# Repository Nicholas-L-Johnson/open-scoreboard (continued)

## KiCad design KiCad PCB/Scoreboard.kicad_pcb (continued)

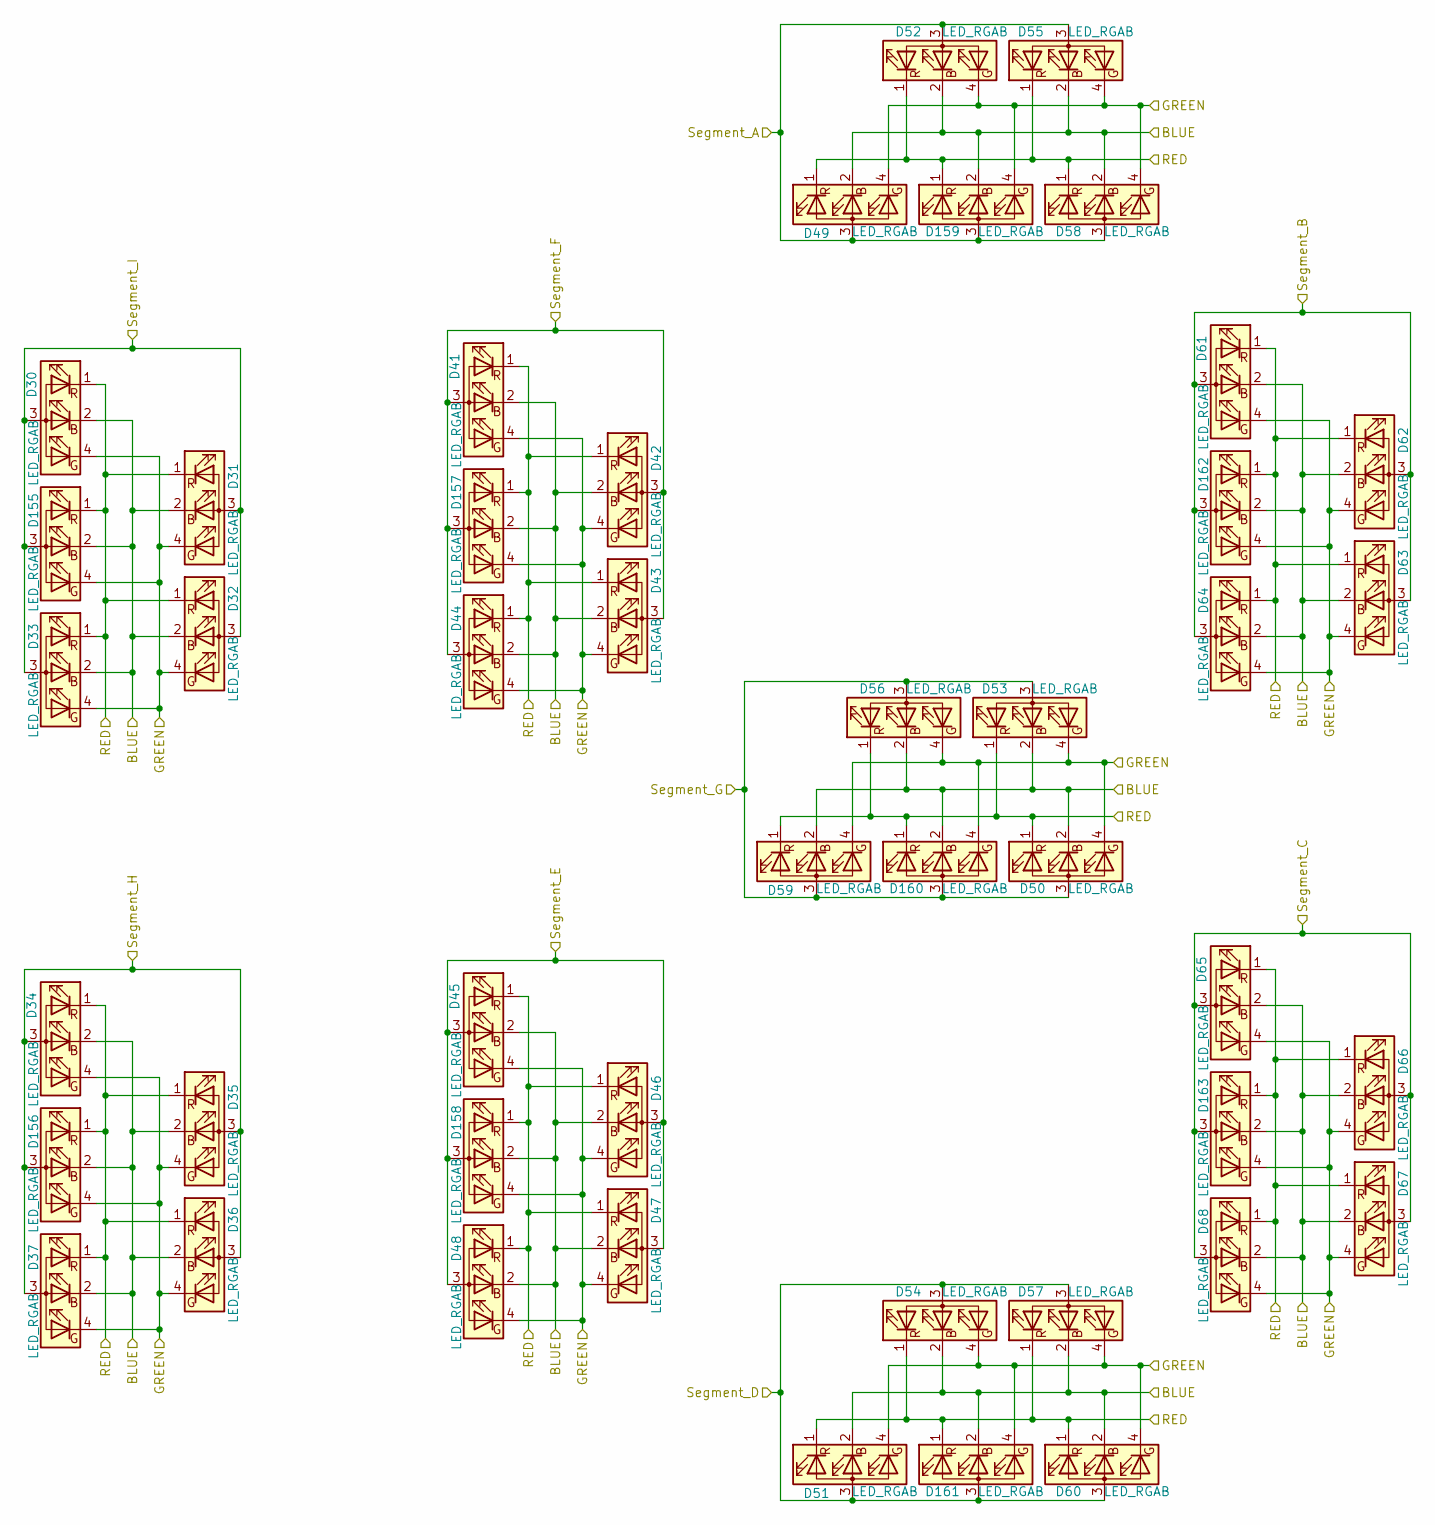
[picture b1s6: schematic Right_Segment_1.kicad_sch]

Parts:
D30, D31, D32, D33, D34, D35, D36, D37, D41, D42, D43, D44, D45, D46, D47, D48, D49, D50, D51, D52, D53, D54, D55, D56, D57, D58, D59, D60, D61, D62, D63, D64, D65, D66, D67, D68, D155, D156, D157, D158, D159, D160, D161, D162, D163: LED_RGAB; RGB_LED_NH-B2020RGBA-HF; Part Number NH-B2020RGBA-HF; LCSC Part Number C2874116

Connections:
BLUE_RIGHT_1: D30.2 (GK), D31.2 (GK), D32.2 (GK), D33.2 (GK), D34.2 (GK), D35.2 (GK), D36.2 (GK), D37.2 (GK), D41.2 (GK), D42.2 (GK), D43.2 (GK), D44.2 (GK), D45.2 (GK), D46.2 (GK), D47.2 (GK), D48.2 (GK), D49.2 (GK), D50.2 (GK), D51.2 (GK), D52.2 (GK), D53.2 (GK), D54.2 (GK), D55.2 (GK), D56.2 (GK), D57.2 (GK), D58.2 (GK), D59.2 (GK), D60.2 (GK), D61.2 (GK), D62.2 (GK), D63.2 (GK), D64.2 (GK), D65.2 (GK), D66.2 (GK), D67.2 (GK), D68.2 (GK), D155.2 (GK), D156.2 (GK), D157.2 (GK), D158.2 (GK), D159.2 (GK), D160.2 (GK), D161.2 (GK), D162.2 (GK), D163.2 (GK); also elsewhere on the board
GREEN_RIGHT_1: D30.4 (BK), D31.4 (BK), D32.4 (BK), D33.4 (BK), D34.4 (BK), D35.4 (BK), D36.4 (BK), D37.4 (BK), D41.4 (BK), D42.4 (BK), D43.4 (BK), D44.4 (BK), D45.4 (BK), D46.4 (BK), D47.4 (BK), D48.4 (BK), D49.4 (BK), D50.4 (BK), D51.4 (BK), D52.4 (BK), D53.4 (BK), D54.4 (BK), D55.4 (BK), D56.4 (BK), D57.4 (BK), D58.4 (BK), D59.4 (BK), D60.4 (BK), D61.4 (BK), D62.4 (BK), D63.4 (BK), D64.4 (BK), D65.4 (BK), D66.4 (BK), D67.4 (BK), D68.4 (BK), D155.4 (BK), D156.4 (BK), D157.4 (BK), D158.4 (BK), D159.4 (BK), D160.4 (BK), D161.4 (BK), D162.4 (BK), D163.4 (BK); also elsewhere on the board
RED_RIGHT_1: D30.1 (RK), D31.1 (RK), D32.1 (RK), D33.1 (RK), D34.1 (RK), D35.1 (RK), D36.1 (RK), D37.1 (RK), D41.1 (RK), D42.1 (RK), D43.1 (RK), D44.1 (RK), D45.1 (RK), D46.1 (RK), D47.1 (RK), D48.1 (RK), D49.1 (RK), D50.1 (RK), D51.1 (RK), D52.1 (RK), D53.1 (RK), D54.1 (RK), D55.1 (RK), D56.1 (RK), D57.1 (RK), D58.1 (RK), D59.1 (RK), D60.1 (RK), D61.1 (RK), D62.1 (RK), D63.1 (RK), D64.1 (RK), D65.1 (RK), D66.1 (RK), D67.1 (RK), D68.1 (RK), D155.1 (RK), D156.1 (RK), D157.1 (RK), D158.1 (RK), D159.1 (RK), D160.1 (RK), D161.1 (RK), D162.1 (RK), D163.1 (RK); also elsewhere on the board
Segment_A: D49.3 (A), D52.3 (A), D55.3 (A), D58.3 (A), D159.3 (A); also elsewhere on the board
Segment_B: D61.3 (A), D62.3 (A), D63.3 (A), D64.3 (A), D162.3 (A); also elsewhere on the board
Segment_C: D65.3 (A), D66.3 (A), D67.3 (A), D68.3 (A), D163.3 (A); also elsewhere on the board
Segment_D: D51.3 (A), D54.3 (A), D57.3 (A), D60.3 (A), D161.3 (A); also elsewhere on the board
Segment_E: D45.3 (A), D46.3 (A), D47.3 (A), D48.3 (A), D158.3 (A); also elsewhere on the board
Segment_F: D41.3 (A), D42.3 (A), D43.3 (A), D44.3 (A), D157.3 (A); also elsewhere on the board
Segment_G: D50.3 (A), D53.3 (A), D56.3 (A), D59.3 (A), D160.3 (A); also elsewhere on the board
Segment_H: D34.3 (A), D35.3 (A), D36.3 (A), D37.3 (A), D156.3 (A); also elsewhere on the board
Segment_I: D30.3 (A), D31.3 (A), D32.3 (A), D33.3 (A), D155.3 (A); also elsewhere on the board

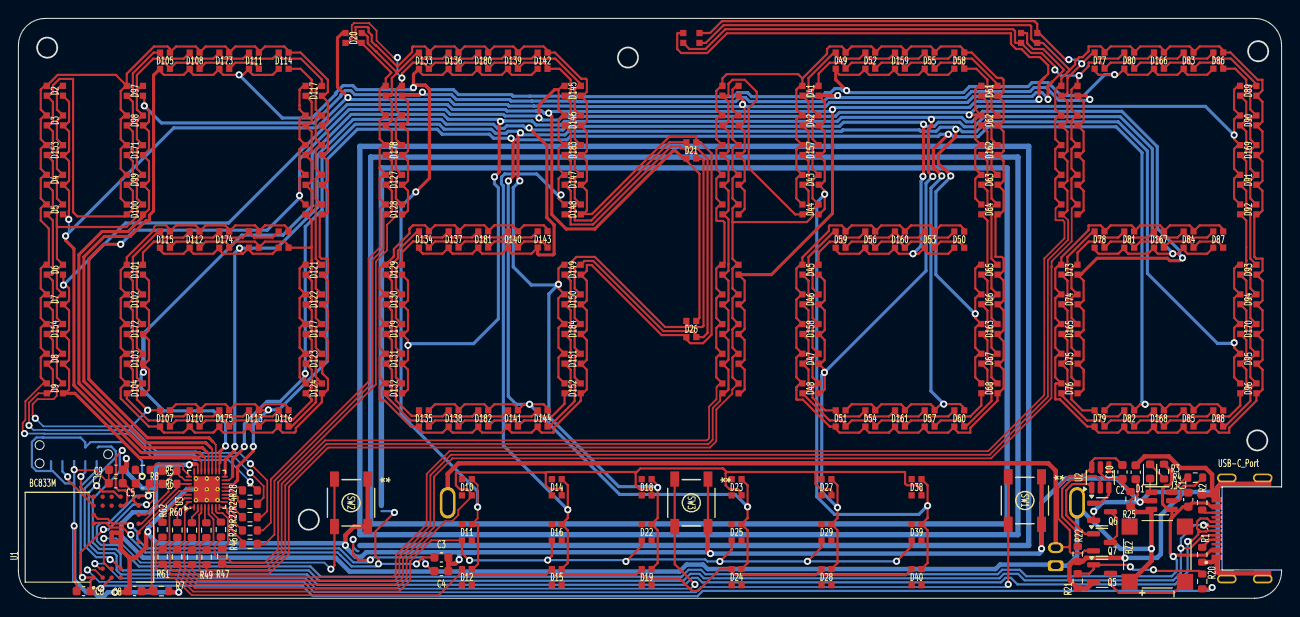
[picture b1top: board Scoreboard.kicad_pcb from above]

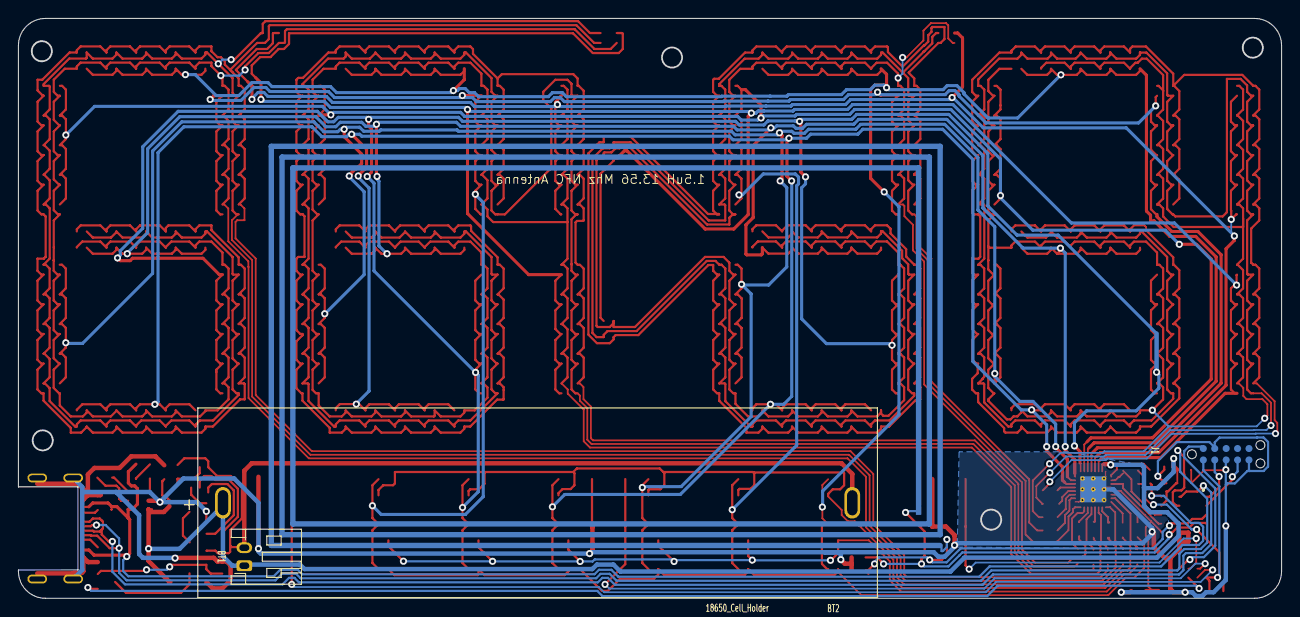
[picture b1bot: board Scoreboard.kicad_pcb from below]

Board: 2 copper layers, 140.5 x 64.5 mm, 237 parts (4 on the bottom side), 72 nets.

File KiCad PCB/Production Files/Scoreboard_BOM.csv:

"#","Reference","Value","Datasheet","Footprint","Qty","Manufacturer","Package","Price","Vendor","DNP","Notes","Part Number","LCSC Part Number","Website"
"1","BT2","18650_Cell_Holder","https://www.lcsc.com/datasheet/lcsc_datasheet_2211291730_MYO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","User_Footprints:18650_Cell_Holder","1","MYOUNG","THT",".42","LCSC","DNP","","BH-18650-A1AJ005","C5290176","https://www.lcsc.com/product-detail/Button-And-Strip-Battery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"
"2","BZ2","Buzzer","https://www.lcsc.com/datasheet/lcsc_datasheet_2410010301_KEL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","User_Footprints:XDCR_CMT-7525-80-SMT-TR","1","KELIKING","SMD",".4741","LCSC","","2-4.5V 85dB 2.731kHz","KLJ-7525-3627","C189208","https://www.lcsc.com/product-detail/Buzzers_KELIKING-KLJ-752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"
"3","C1,C2,C9","1u","https://datasheet.lcsc.com/lcsc/2209191700_Samsung-Electro-M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","User_Footprints:C_0603_1608Metric","3","Samsung Electro-Mechanics","0603",".0032","LCSC","","16V 10%","CL10A105KO8NNNC","C1592","https://www.lcsc.com/product-detail/Multilayer-Ceramic-Capac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"
"4","C3,C4","18p","https://datasheet.lcsc.com/lcsc/2208181800_FOJAN-FCC0603N180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","User_Footprints:C_0603_1608Metric","2","FOJAN","0603",".0027","LCSC","","50V 5%","FCC0603N180J500CT","C5137620","https://www.lcsc.com/product-detail/Multilayer-Ceramic-Capac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"
"5","C5,C6","4u7","https://datasheet.lcsc.com/lcsc/2208051100_HRE-CSA0603X5R475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","User_Footprints:C_0603_1608Metric","2","HRE","0603",".0050","LCSC","","6.3V 10%","CGA0603X5R475K6R3JT","C7503506","https://www.lcsc.com/product-detail/Multilayer-Ceramic-Capac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"
"6","C7,C8,C10","100n","https://datasheet.lcsc.com/lcsc/2304140030_Samsung-Electro-M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","Capacitor_SMD:C_0603_1608Metric","3","Samsung Electro-Mechanics","0603",".0028","LCSC","","25V 10%","CL10B104KA8NNNC","C1590","https://www.lcsc.com/product-detail/Multilayer-Ceramic-Capac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"
"7","D1","LED","https://www.lcsc.com/datasheet/lcsc_datasheet_2402181505_XIN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","LED_SMD:LED_0603_1608Metric","1","XINGLIGHT","0603",".003","LCSC","","20mA","XL-1608SURC-06","C965799","https://www.lcsc.com/product-detail/span-style-background-co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"
"8","D2,D3,D4,D5,D6,D7,D8,D9,D10,D11,D12,D13,D14,D15,D16,D17,D18,D19,D20,D21,D22,D23,D24,D25,D26,D27,D28,D29,D30,D31,D32,D33,D34,D35,D36,D37,D38,D39,D40,D41,D42,D43,D44,D45,D46,D47,D48,D49,D50,D51,D52,D53,D54,D55,D56,D57,D58,D59,D60,D61,D62,D63,D64,D65,D66,D67,D68,D69,D70,D71,D72,D73,D74,D75,D76,D77,D78,D79,D80,D81,D82,D83,D84,D85,D86,D87,D88,D89,D90,D91,D92,D93,D94,D95,D96,D97,D98,D99,D100,D101,D102,D103,D104,D105,D106,D107,D108,D109,D110,D111,D112,D113,D114,D115,D116,D117,D118,D119,D120,D121,D122,D123,D124,D125,D126,D127,D128,D129,D130,D131,D132,D133,D134,D135,D136,D137,D138,D139,D140,D141,D142,D143,D144,D145,D146,D147,D148,D149,D150,D151,D152,D153,D154,D155,D156,D157,D158,D159,D160,D161,D162,D163,D164,D165,D166,D167,D168,D169,D170,D171,D172,D173,D174,D175,D176,D177,D178,D179,D180,D181,D182,D183,D184","LED_RGAB","https://datasheet.lcsc.com/lcsc/2108150330_Foshan-NationStar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","User_Footprints:RGB_LED_NH-B2020RGBA-HF","183","Foshan NationStar Optoelectronics","LED RGAB 2020",".0081","LCSC","","SMD","NH-B2020RGBA-HF","C2874116","https://www.lcsc.com/product-detail/Light-Emitting-Diodes-LE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"
"9","J2","USB-C_Port","https://www.lcsc.com/datasheet/lcsc_datasheet_2312191005_G-S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","User_Footprints:GCT_USB4110GFA","1","G-Switch","SMD",".0952","LCSC","","5A","GT-USB-7014A","C963371","https://www.lcsc.com/product-detail/USB-Connectors_G-Switch-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"
"10","J3","TP4057","https://www.vishay.com/docs/83316/sot236l.pdf","User_Footprints:SOT-23-6","1","YONGYUTAI","SOT-23-6L",".0265","LCSC","","0.3V-6.5V 600mA","TP4057","C20199358","https://www.lcsc.com/product-detail/Battery-Management_YONGY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"
"11","Q5,Q6,Q7","HL-2302V","https://datasheet.lcsc.com/lcsc/2306211455_HL-2302V_C7431443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","Package_TO_SOT_SMD:SOT-23","3","HL","SOT-23",".0089","LCSC","","N-Channel 3A Mosfet","2302V","C7431443","https://www.lcsc.com/product-detail/MOSFETs_HL-2302V_C7431443.html"
"12","R8","10K","https://www.lcsc.com/datasheet/lcsc_datasheet_2411071710_FOJ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","User_Footprints:R_0603_1608Metric","1","FOJAN","0603",".0008","LCSC","","100mW 5%","FRC0603J103 TS","C2930027","https://www.lcsc.com/product-detail/Chip-Resistor-Surface-Mo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"
"13","R25","100","https://www.lcsc.com/datasheet/lcsc_datasheet_2411071710_FOJ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","User_Footprints:R_0603_1608Metric","1","FOJAN","0603",".0008","LCSC","","100mW 5%","FRC0603J101 TS","C2907089","https://www.lcsc.com/product-detail/Chip-Resistor-Surface-Mo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"
"14","R1,R2,R4","5K1","https://datasheet.lcsc.com/lcsc/2304140030_YAGEO-RC0603FR-07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","User_Footprints:R_0603_1608Metric","3","YAGEO","0603",".0013","LCSC","","100mW 1%","RC0603FR-075K1L","C105580","https://www.lcsc.com/product-detail/Chip-Resistor-Surface-Mo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"
"15","R24,R27,R46,R48,R49,R50,R58,R59,R60,R62","21","https://datasheet.lcsc.com/lcsc/2308241947_FOJAN-FRC0603F21R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","User_Footprints:R_0603_1608Metric","10","FOJAN","0603",".0009","LCSC","","100mW 1%","FRC0603F21R0TS","C5713281","https://www.lcsc.com/product-detail/Chip-Resistor-Surface-Mo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"
"16","R28,R29,R47,R51,R61","43","https://datasheet.lcsc.com/lcsc/2308241947_FOJAN-FRC0603F43R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","User_Footprints:R_0603_1608Metric","5","FOJAN","0603",".0009","LCSC","","100mW 1%","FRC0603F43R0TS","C2907039","https://www.lcsc.com/product-detail/Chip-Resistor-Surface-Mo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"
"17","R3,R20,R22","1K","https://datasheet.lcsc.com/lcsc/2308241947_FOJAN-FRC0603J102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","User_Footprints:R_0603_1608Metric","3","FOJAN","0603",".0008","LCSC","","100mW 1%","FRC0603J102 TS","C2907113","https://www.lcsc.com/product-detail/Chip-Resistor-Surface-Mo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"
"18","R5,R6","2K","https://www.lcsc.com/datasheet/lcsc_datasheet_2411071710_FOJ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","User_Footprints:R_0603_1608Metric","2","Fojan","0603",".0008","LCSC","","100mW 5%","FRC0603J202 TS","C2907137","https://www.lcsc.com/product-detail/Chip-Resistor-Surface-Mo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"
"19","R7,R21","100K","https://www.lcsc.com/datasheet/lcsc_datasheet_2411071710_FOJ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","User_Footprints:R_0603_1608Metric","2","FOJAN","0603",".0007","LCSC","","100mW 5%","FRC0603J104 TS","C2907088","https://www.lcsc.com/product-detail/Chip-Resistor-Surface-Mo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"
"20","SW1,SW2,SW3","SW_Push","https://www.lcsc.com/datasheet/lcsc_datasheet_2110151630_XKB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","User_Footprints:SW4_1437565_TEC","3","XKB Connection","SMD",".0368","LCSC","","50mA","TS-1187A-C-D-B","C318888","https://www.lcsc.com/product-detail/Tactile-Switches_XKB-Con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"
"21","U1","BC833M","https://static1.squarespace.com/static/561459a2e4b0b39f5cefa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","User_Footprints:XCVR_BC833M","1","Fanstel Corp.","SMD","5.00","LCSC","","nRF52833","BC833M","","https://www.fanstel.com/bc833"
"22","U2","DW01A","https://www.lcsc.com/datasheet/lcsc_datasheet_2411121620_Slk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","Package_TO_SOT_SMD:SOT-23-6","1","Slkor","SOT-23-6",".0164","LCSC","","SMD","DW01A","C318888","https://www.lcsc.com/product-detail/Battery-Management_Slkor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"
"23","U3","IS31FL3729","https://www.lcsc.com/datasheet/lcsc_datasheet_2410121548_ISS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","Package_DFN_QFN:QFN-32-1EP_4x4mm_P0.4mm_EP2.9x2.9mm_ThermalVias","1","Integrated Silicon Solution (ISSI)","QFN-32-EP(4x4)",".94","LCSC","","SMD","IS31FL3729-QFLS4-TR","C2940549","https://www.lcsc.com/product-detail/LED-Drivers_ISSI-Integra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"

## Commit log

2025-08-11 started combining repos into one project
2025-08-11 added the app and a folder for images/video
2025-08-11 fixed app directory
2025-08-11 remove DS_Store
2025-08-11 Added images to the media folder
2025-08-11 Cropped the images
